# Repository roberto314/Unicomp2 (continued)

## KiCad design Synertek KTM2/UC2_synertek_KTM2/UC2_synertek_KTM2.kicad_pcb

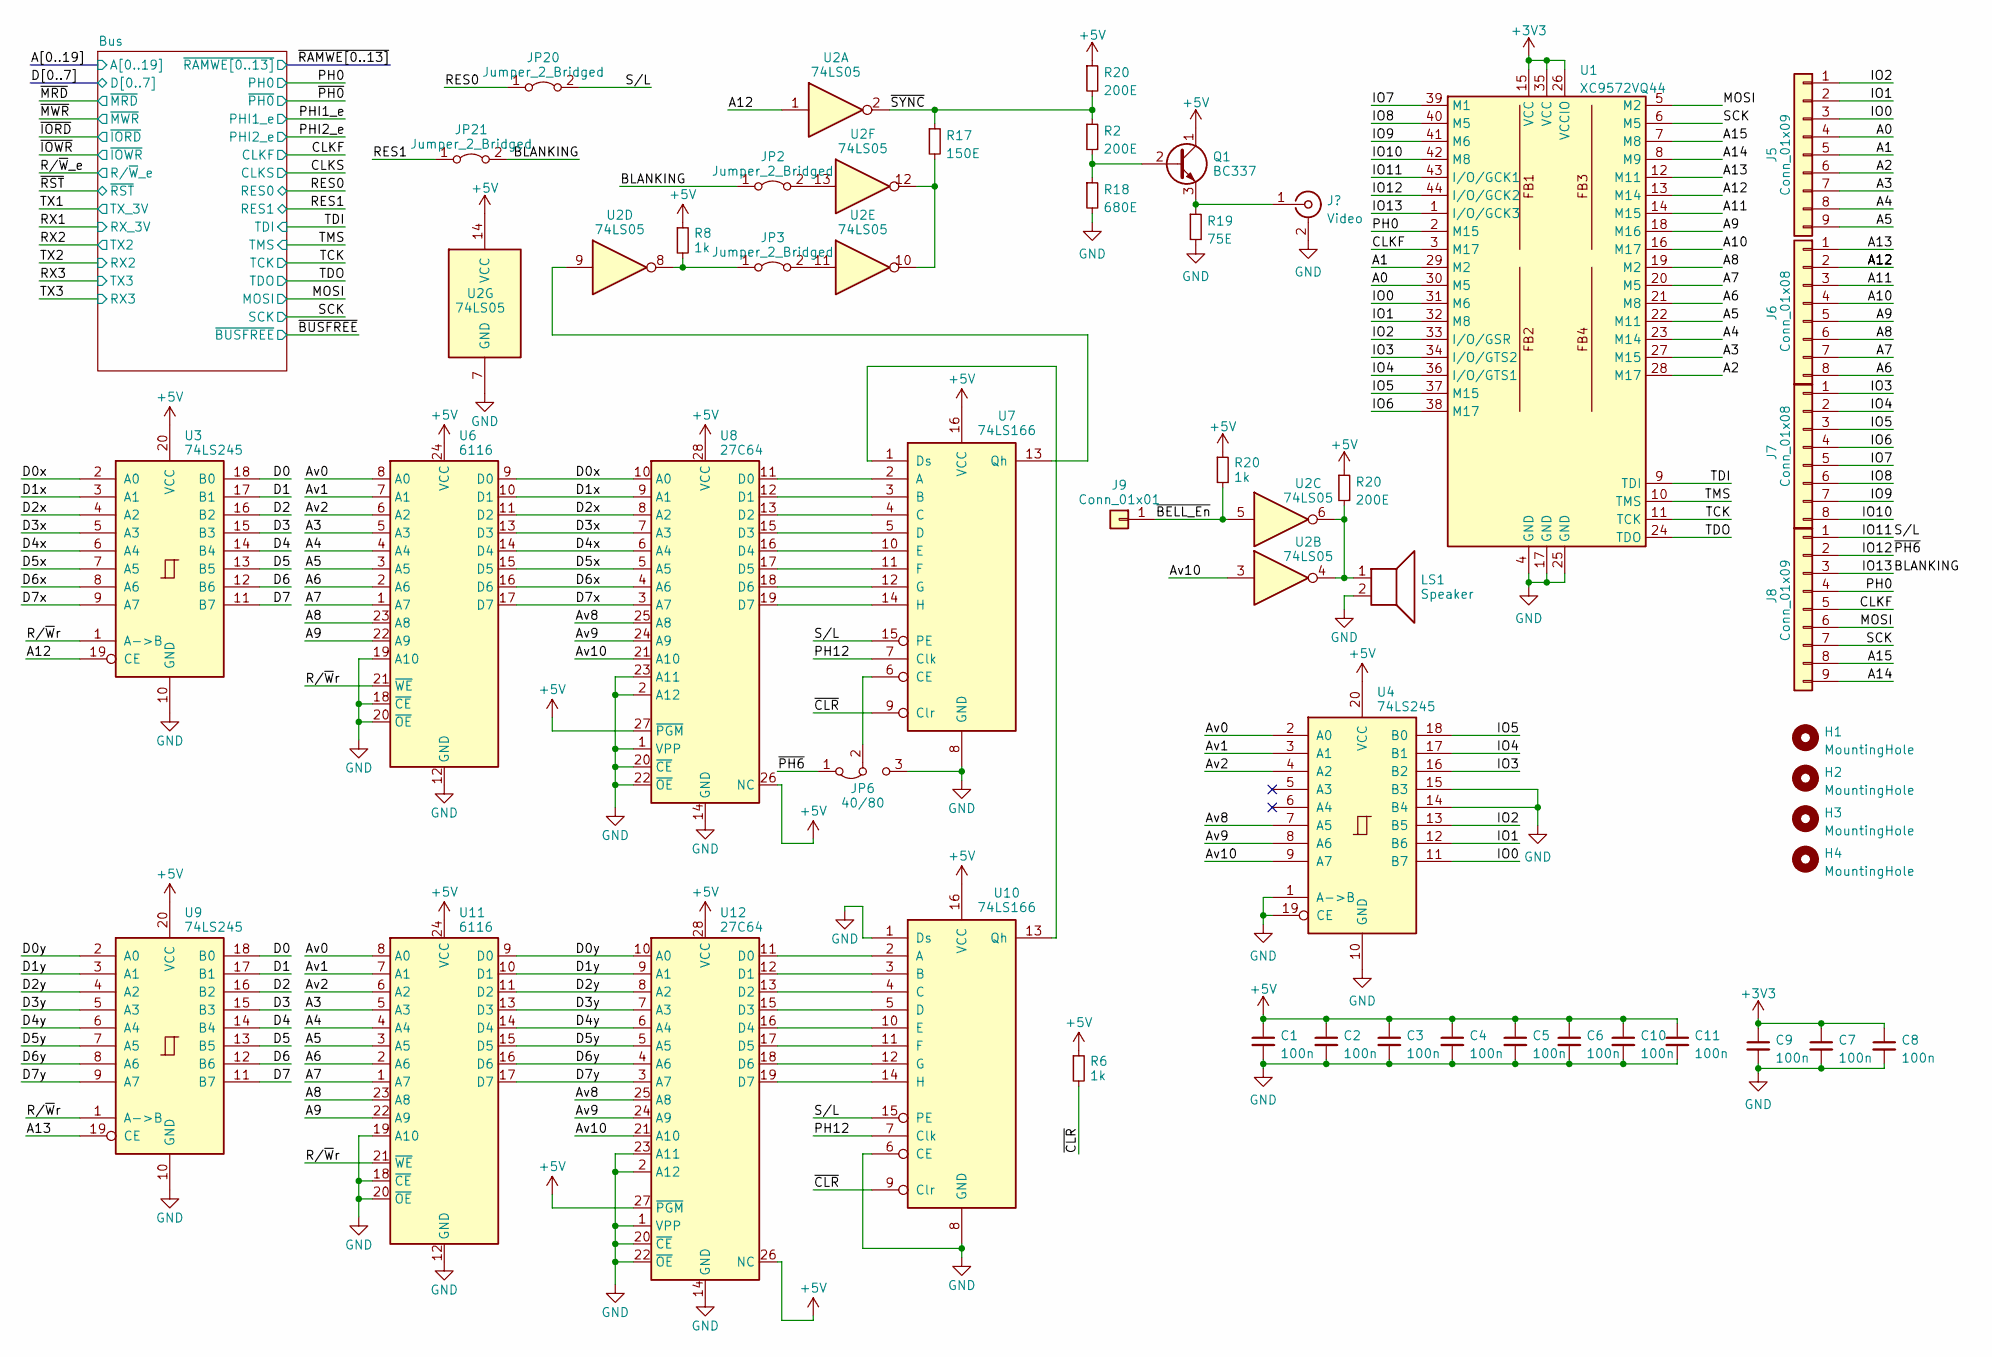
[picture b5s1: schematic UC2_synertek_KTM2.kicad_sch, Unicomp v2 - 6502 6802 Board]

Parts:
C1, C2, C3, C4, C5, C6, C7, C8, C9, C10, C11: 100n; C_1206_3216Metric
H1, H2, H3, H4: MountingHole; MountingHole_3.2mm_M3
J5, J8: Conn_01x09; PinHeader_1x09_P2.54mm_Vertical
J6, J7: Conn_01x08; PinHeader_1x08_P2.54mm_Vertical
J9: Conn_01x01; PinHeader_1x01_P2.54mm_Vertical
J20: Video; RCA-Jack
JP2, JP3, JP20, JP21: Jumper_2_Bridged; SolderJumper-2_P1.3mm_Bridged_RoundedPad1.0x1.5mm
JP6: 40/80; SolderJumper-3_P1.3mm_Bridged12_Pad1.0x1.5mm_NumberLabels
LS1: Speaker; MagneticBuzzer_Kingstate_KCG0601
Q1: BC337; TO-92_Inline
R2, R20: 200E; R_1206_3216Metric_Pad1.30x1.75mm_HandSolder
R6, R8: 1k; R_1206_3216Metric_Pad1.30x1.75mm_HandSolder
R17: 150E; R_1206_3216Metric_Pad1.30x1.75mm_HandSolder
R18: 680E; R_1206_3216Metric_Pad1.30x1.75mm_HandSolder
R19: 75E; R_1206_3216Metric_Pad1.30x1.75mm_HandSolder
U1: XC9572VQ44; TQFP-44_10x10mm_P0.8mm
U2: 74LS05; DIP-14_W7.62mm_LongPads
U3, U9: 74LS245; DIP-20_W7.62mm_LongPads
U4: 74LS245; SO-20_5.3x12.6mm_P1.27mm
U6, U11: 6116; DIP-24_W15.24mm_LongPads
U7, U10: 74LS166; DIP-16_W7.62mm_LongPads
U8, U12: 27C64; DIP-28_W15.24mm_LongPads

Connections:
+3V3: C7.1, C8.1, C9.1, U1.15 (VCC), U1.26 (VCCIO), U1.35 (VCC); also elsewhere on the board
+5V: C1.1, C2.1, C3.1, C4.1, C5.1, C6.1, C10.1, C11.1, Q1.1 (C), R6.1, R8.1, R20.1, U2.14 (VCC), U3.20 (VCC), U4.20 (VCC), U6.24 (VCC), U7.16 (VCC), U8.26 (NC), U8.27 (~PGM), U8.28 (VCC), U9.20 (VCC), U10.16 (VCC), U11.24 (VCC), U12.26 (NC), U12.27 (~PGM), U12.28 (VCC); also elsewhere on the board
/A0: J5.4, U1.30 (M5); also elsewhere on the board
/A1: J5.5, U1.29 (M2); also elsewhere on the board
/A2: J5.6, U1.28 (M17); also elsewhere on the board
/A3: J5.7, U1.27 (M15), U6.5 (A3), U11.5 (A3); also elsewhere on the board
/A4: J5.8, U1.23 (M14), U6.4 (A4), U11.4 (A4); also elsewhere on the board
/A5: J5.9, U1.22 (M11), U6.3 (A5), U11.3 (A5); also elsewhere on the board
/A6: J6.8, U1.21 (M8), U6.2 (A6), U11.2 (A6); also elsewhere on the board
/A7: J6.7, U1.20 (M5), U6.1 (A7), U11.1 (A7); also elsewhere on the board
/A8: J6.6, U1.19 (M2), U6.23 (A8), U11.23 (A8); also elsewhere on the board
/A9: J6.5, U1.18 (M16), U6.22 (A9), U11.22 (A9); also elsewhere on the board
/A10: J6.4, U1.16 (M17); also elsewhere on the board
/A11: J6.3, U1.14 (M15); also elsewhere on the board
/A12: J6.2, U1.13 (M14), U2.1, U3.19 (CE); also elsewhere on the board
/A13: J6.1, U1.12 (M11), U9.19 (CE); also elsewhere on the board
/A14: J8.9, U1.8 (M9); also elsewhere on the board
/A15: J8.8, U1.7 (M8); also elsewhere on the board
/Av0: U4.2 (A0), U6.8 (A0), U11.8 (A0)
/Av1: U4.3 (A1), U6.7 (A1), U11.7 (A1)
/Av2: U4.4 (A2), U6.6 (A2), U11.6 (A2)
/Av8: U4.7 (A5), U8.25 (A8), U12.25 (A8)
/Av9: U4.8 (A6), U8.24 (A9), U12.24 (A9)
/Av10: U2.3, U4.9 (A7), U8.21 (A10), U12.21 (A10)
/BLANKING: J8.3, JP2.1 (A), JP21.2 (B), U1.1 (I/O/GCK3)
/CLKF: J8.5, U1.3 (M17); also elsewhere on the board
/D0: U3.18 (B0), U9.18 (B0); also elsewhere on the board
/D0x: U3.2 (A0), U6.9 (D0), U8.10 (A0)
/D0y: U9.2 (A0), U11.9 (D0), U12.10 (A0)
/D1: U3.17 (B1), U9.17 (B1); also elsewhere on the board
/D1x: U3.3 (A1), U6.10 (D1), U8.9 (A1)
/D1y: U9.3 (A1), U11.10 (D1), U12.9 (A1)
/D2: U3.16 (B2), U9.16 (B2); also elsewhere on the board
/D2x: U3.4 (A2), U6.11 (D2), U8.8 (A2)
/D2y: U9.4 (A2), U11.11 (D2), U12.8 (A2)
/D3: U3.15 (B3), U9.15 (B3); also elsewhere on the board
/D3x: U3.5 (A3), U6.13 (D3), U8.7 (A3)
/D3y: U9.5 (A3), U11.13 (D3), U12.7 (A3)
/D4: U3.14 (B4), U9.14 (B4); also elsewhere on the board
/D4x: U3.6 (A4), U6.14 (D4), U8.6 (A4)
/D4y: U9.6 (A4), U11.14 (D4), U12.6 (A4)
/D5: U3.13 (B5), U9.13 (B5); also elsewhere on the board
/D5x: U3.7 (A5), U6.15 (D5), U8.5 (A5)
/D5y: U9.7 (A5), U11.15 (D5), U12.5 (A5)
/D6: U3.12 (B6), U9.12 (B6); also elsewhere on the board
/D6x: U3.8 (A6), U6.16 (D6), U8.4 (A6)
/D6y: U9.8 (A6), U11.16 (D6), U12.4 (A6)
/D7: U3.11 (B7), U9.11 (B7); also elsewhere on the board
/D7x: U3.9 (A7), U6.17 (D7), U8.3 (A7)
/D7y: U9.9 (A7), U11.17 (D7), U12.3 (A7)
/IO0: J5.3, U1.31 (M6), U4.11 (B7)
/IO1: J5.2, U1.32 (M8), U4.12 (B6)
/IO2: J5.1, U1.33 (I/O/GSR), U4.13 (B5)
/IO3: J7.1, U1.34 (I/O/GTS2), U4.16 (B2)
/IO4: J7.2, U1.36 (I/O/GTS1), U4.17 (B1)
/IO5: J7.3, U1.37 (M15), U4.18 (B0)
/IO6: J7.4, U1.38 (M17)
/IO7: J7.5, U1.39 (M1)
/IO8: J7.6, U1.40 (M5)
/IO9: J7.7, U1.41 (M6)
/IO10: J7.8, U1.42 (M8)
/IO11: J8.1, JP20.2 (B), U1.43 (I/O/GCK1), U7.15 (PE), U10.15 (PE)
/IO12: J8.2, JP6.1 (A), U1.44 (I/O/GCK2)
/MOSI: J8.6, U1.5 (M2); also elsewhere on the board
/PH0: J8.4, U1.2 (M15); also elsewhere on the board
/PH12: U7.7 (Clk), U10.7 (Clk)
/RES0: JP20.1 (A); also elsewhere on the board
/RES1: JP21.1 (A); also elsewhere on the board
/R/~Wr: U3.1 (A->B), U6.21 (~WE), U9.1 (A->B), U11.21 (~WE)
/SCK: J8.7, U1.6 (M5); also elsewhere on the board
/TCK: U1.11 (TCK); also elsewhere on the board
/TDI: U1.9 (TDI); also elsewhere on the board
/TDO: U1.24 (TDO); also elsewhere on the board
/TMS: U1.10 (TMS); also elsewhere on the board
/~CLR: R6.2, U7.9 (Clr), U10.9 (Clr)
GND: C1.2, C2.2, C3.2, C4.2, C5.2, C6.2, C7.2, C8.2, C9.2, C10.2, C11.2, J20.2 (Ext), JP6.3 (B), LS1.2, R18.2, R19.2, U1.4 (GND), U1.17 (GND), U1.25 (GND), U2.7 (GND), U3.10 (GND), U4.1 (A->B), U4.10 (GND), U4.14 (B4), U4.15 (B3), U4.19 (CE), U6.12 (GND), U6.18 (~CE), U6.19 (A10), U6.20 (~OE), U7.8 (GND), U8.1 (VPP), U8.2 (A12), U8.14 (GND), U8.20 (~CE), U8.22 (~OE), U8.23 (A11), U9.10 (GND), U10.1 (Ds), U10.6 (CE), U10.8 (GND), U11.12 (GND), U11.18 (~CE), U11.19 (A10), U11.20 (~OE), U12.1 (VPP), U12.2 (A12), U12.14 (GND), U12.20 (~CE), U12.22 (~OE), U12.23 (A11); also elsewhere on the board
unnamed: J20.1 (In), Q1.3 (E), R19.1
unnamed: JP2.2 (B), U2.13
unnamed: JP3.1 (A), R8.2, U2.8
unnamed: JP3.2 (B), U2.11
unnamed: JP6.2 (C), U7.6 (CE)
unnamed: Q1.2 (B), R2.2, R18.1
unnamed: R17.2, U2.10, U2.12
unnamed: U7.2 (A), U8.11 (D0)
unnamed: U7.3 (B), U8.12 (D1)
unnamed: U7.4 (C), U8.13 (D2)
unnamed: U7.5 (D), U8.15 (D3)
unnamed: U7.10 (E), U8.16 (D4)
unnamed: U7.11 (F), U8.17 (D5)
unnamed: U7.12 (G), U8.18 (D6)
unnamed: U7.14 (H), U8.19 (D7)
unnamed: U2.9, U7.13 (Qh)
unnamed: U10.2 (A), U12.11 (D0)
unnamed: U10.3 (B), U12.12 (D1)
unnamed: U10.4 (C), U12.13 (D2)
unnamed: U10.5 (D), U12.15 (D3)
unnamed: U10.10 (E), U12.16 (D4)
unnamed: U10.11 (F), U12.17 (D5)
unnamed: U10.12 (G), U12.18 (D6)
unnamed: U10.14 (H), U12.19 (D7)
unnamed: U7.1 (Ds), U10.13 (Qh)

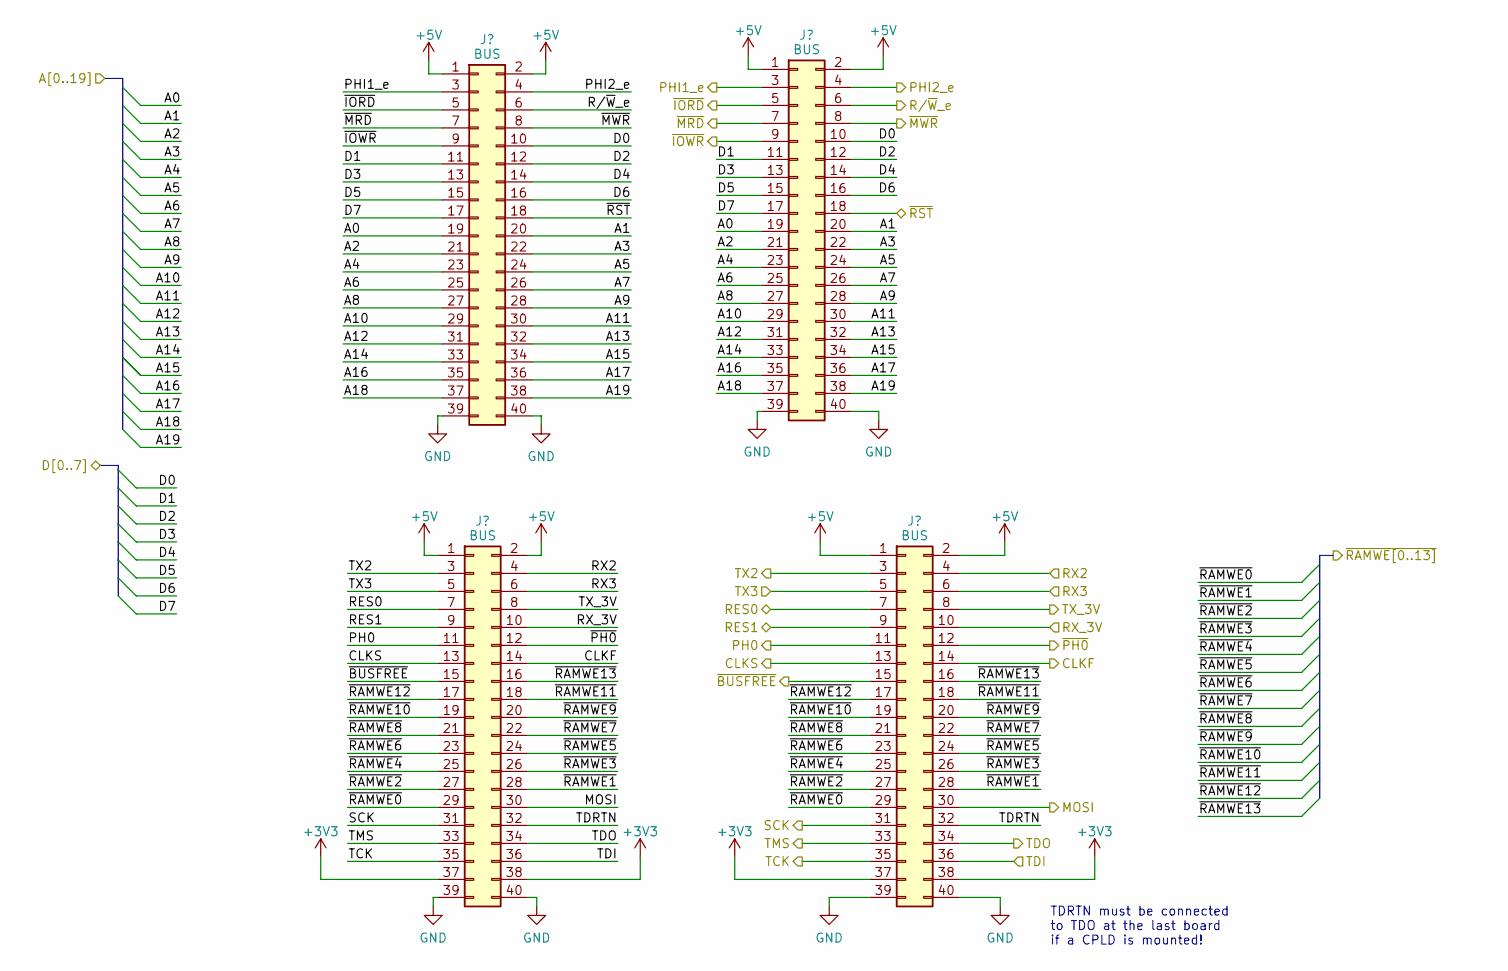
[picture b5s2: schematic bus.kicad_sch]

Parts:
J1, J2, J3, J4: BUS; PinSocket_2x20_P2.54mm_Vertical

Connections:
+3V3: J2.37, J2.38, J4.37, J4.38; also elsewhere on the board
+5V: J1.1, J1.2, J2.1, J2.2, J3.1, J3.2, J4.1, J4.2; also elsewhere on the board
/A0: J1.19, J3.19; also elsewhere on the board
/A1: J1.20, J3.20; also elsewhere on the board
/A2: J1.21, J3.21; also elsewhere on the board
/A3: J1.22, J3.22; also elsewhere on the board
/A4: J1.23, J3.23; also elsewhere on the board
/A5: J1.24, J3.24; also elsewhere on the board
/A6: J1.25, J3.25; also elsewhere on the board
/A7: J1.26, J3.26; also elsewhere on the board
/A8: J1.27, J3.27; also elsewhere on the board
/A9: J1.28, J3.28; also elsewhere on the board
/A10: J1.29, J3.29; also elsewhere on the board
/A11: J1.30, J3.30; also elsewhere on the board
/A12: J1.31, J3.31; also elsewhere on the board
/A13: J1.32, J3.32; also elsewhere on the board
/A14: J1.33, J3.33; also elsewhere on the board
/A15: J1.34, J3.34; also elsewhere on the board
/A16: J1.35, J3.35
/A17: J1.36, J3.36
/A18: J1.37, J3.37
/A19: J1.38, J3.38
/Bus/TDRTN: J2.32, J4.32
/CLKF: J2.14, J4.14; also elsewhere on the board
/CLKS: J2.13, J4.13
/D0: J1.10, J3.10; also elsewhere on the board
/D1: J1.11, J3.11; also elsewhere on the board
/D2: J1.12, J3.12; also elsewhere on the board
/D3: J1.13, J3.13; also elsewhere on the board
/D4: J1.14, J3.14; also elsewhere on the board
/D5: J1.15, J3.15; also elsewhere on the board
/D6: J1.16, J3.16; also elsewhere on the board
/D7: J1.17, J3.17; also elsewhere on the board
/MOSI: J2.30, J4.30; also elsewhere on the board
/PH0: J2.11, J4.11; also elsewhere on the board
/PHI1_e: J1.3, J3.3
/PHI2_e: J1.4, J3.4
/RES0: J2.7, J4.7; also elsewhere on the board
/RES1: J2.9, J4.9; also elsewhere on the board
/RX1: J2.10, J4.10
/RX2: J2.3, J4.3
/RX3: J2.5, J4.5
/R/~W_e: J1.6, J3.6
/SCK: J2.31, J4.31; also elsewhere on the board
/TCK: J2.35, J4.35; also elsewhere on the board
/TDI: J2.36, J4.36; also elsewhere on the board
/TDO: J2.34, J4.34; also elsewhere on the board
/TMS: J2.33, J4.33; also elsewhere on the board
/TX1: J2.8, J4.8
/TX2: J2.4, J4.4
/TX3: J2.6, J4.6
/~BUSFREE: J2.15, J4.15
/~IORD: J1.5, J3.5
/~IOWR: J1.9, J3.9
/~MRD: J1.7, J3.7
/~MWR: J1.8, J3.8
/~PH0: J2.12, J4.12
/~RAMWE0: J2.29, J4.29
/~RAMWE1: J2.28, J4.28
/~RAMWE2: J2.27, J4.27
/~RAMWE3: J2.26, J4.26
/~RAMWE4: J2.25, J4.25
/~RAMWE5: J2.24, J4.24
/~RAMWE6: J2.23, J4.23
/~RAMWE7: J2.22, J4.22
/~RAMWE8: J2.21, J4.21
/~RAMWE9: J2.20, J4.20
/~RAMWE10: J2.19, J4.19
/~RAMWE11: J2.18, J4.18
/~RAMWE12: J2.17, J4.17
/~RAMWE13: J2.16, J4.16
/~RST: J1.18, J3.18
GND: J1.39, J1.40, J2.39, J2.40, J3.39, J3.40, J4.39, J4.40; also elsewhere on the board

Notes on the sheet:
TDRTN must be connected to TDO at the last board if a CPLD is mounted!

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
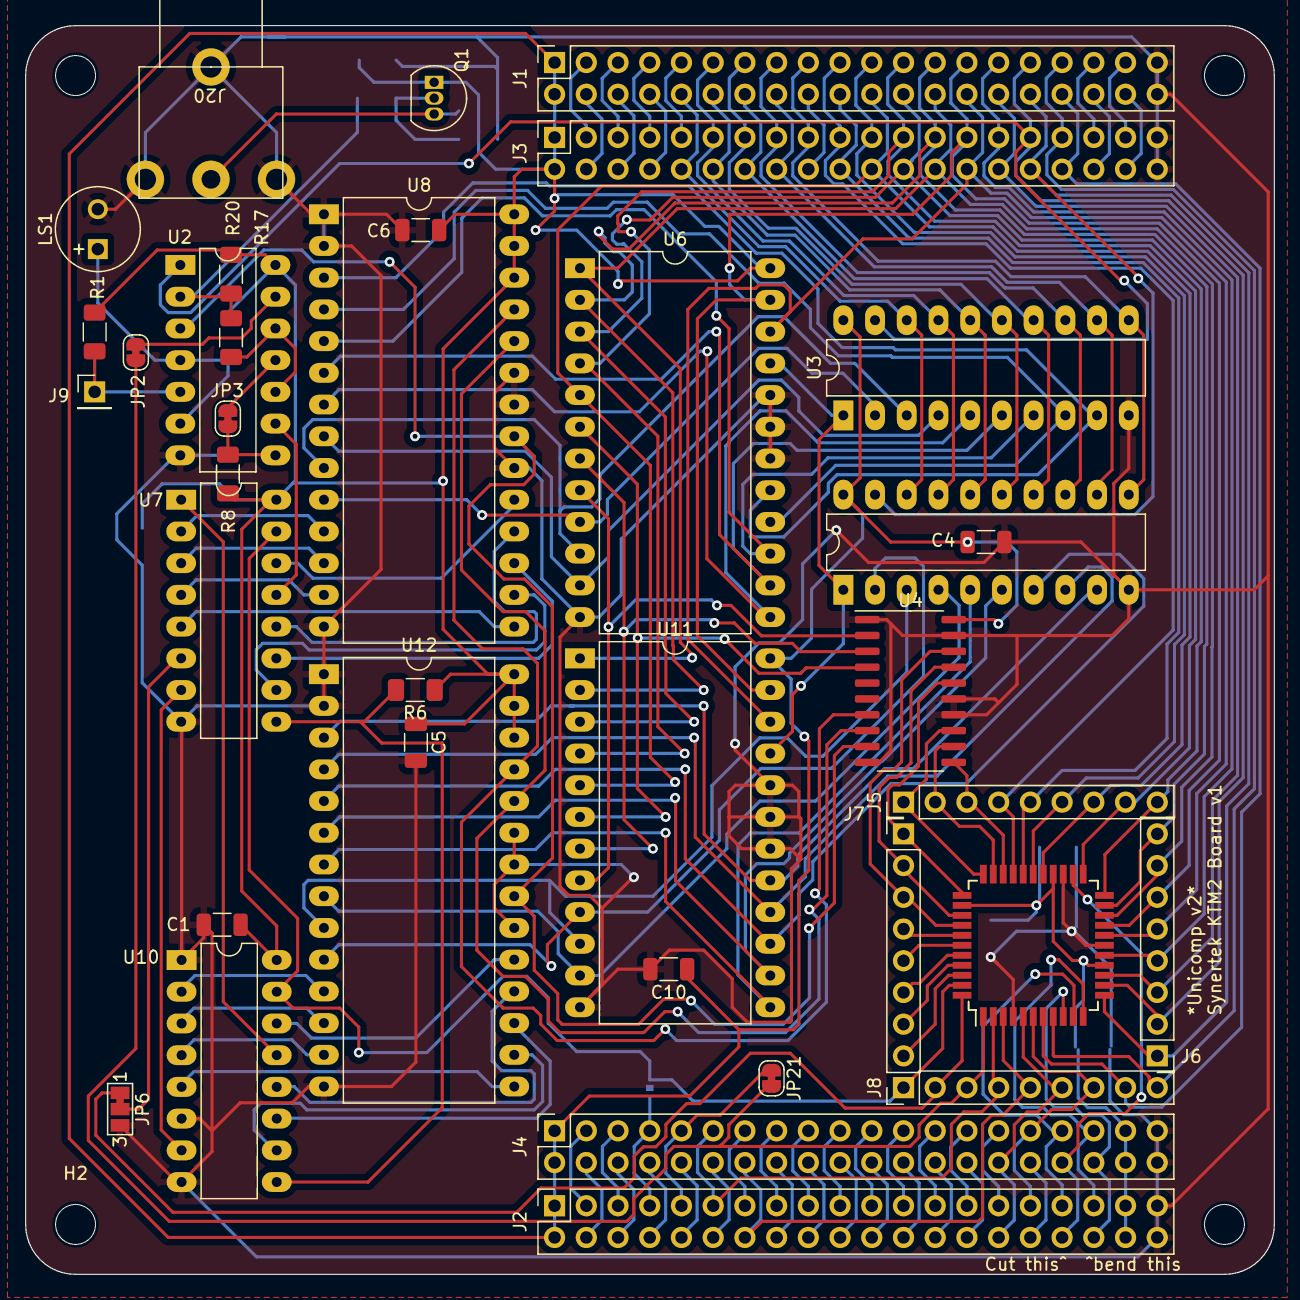
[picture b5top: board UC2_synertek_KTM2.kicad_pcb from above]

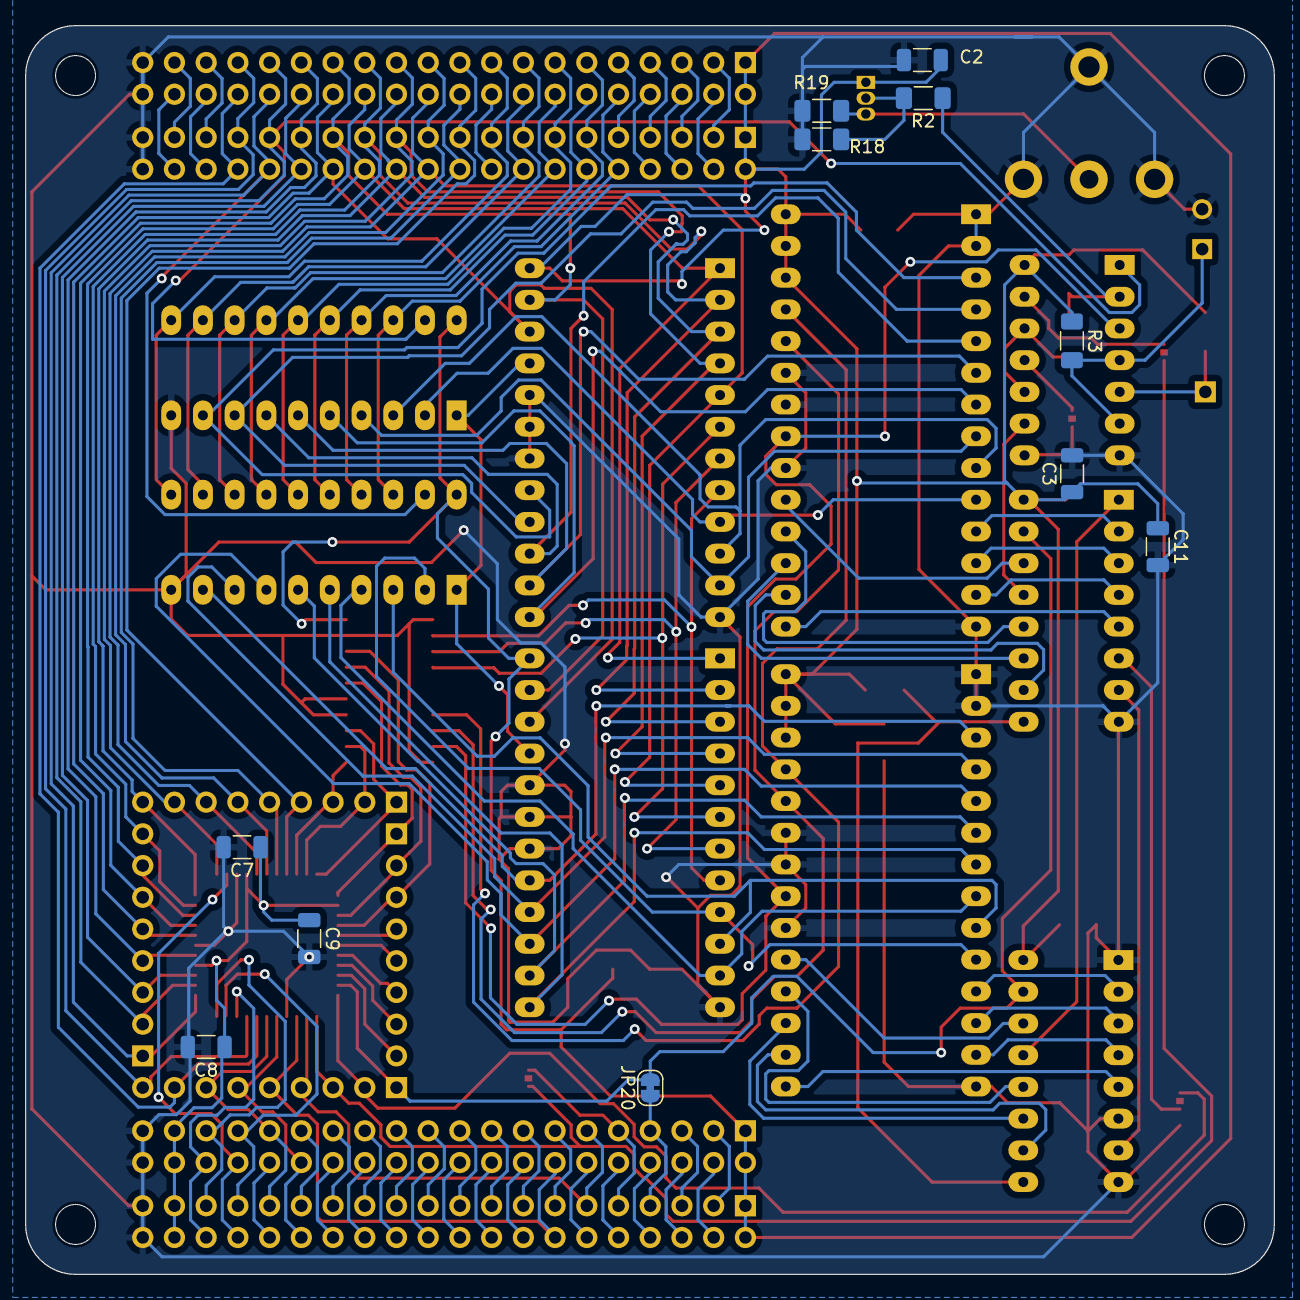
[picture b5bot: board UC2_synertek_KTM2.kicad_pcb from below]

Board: 2 copper layers, 100.0 x 100.0 mm, 52 parts (11 on the bottom side), 140 nets.

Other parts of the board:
R1: 1k; R_1206_3216Metric_Pad1.30x1.75mm_HandSolder
R3: 200E; R_1206_3216Metric_Pad1.30x1.75mm_HandSolder

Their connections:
+5V: R1.1, R3.1; also elsewhere on the board

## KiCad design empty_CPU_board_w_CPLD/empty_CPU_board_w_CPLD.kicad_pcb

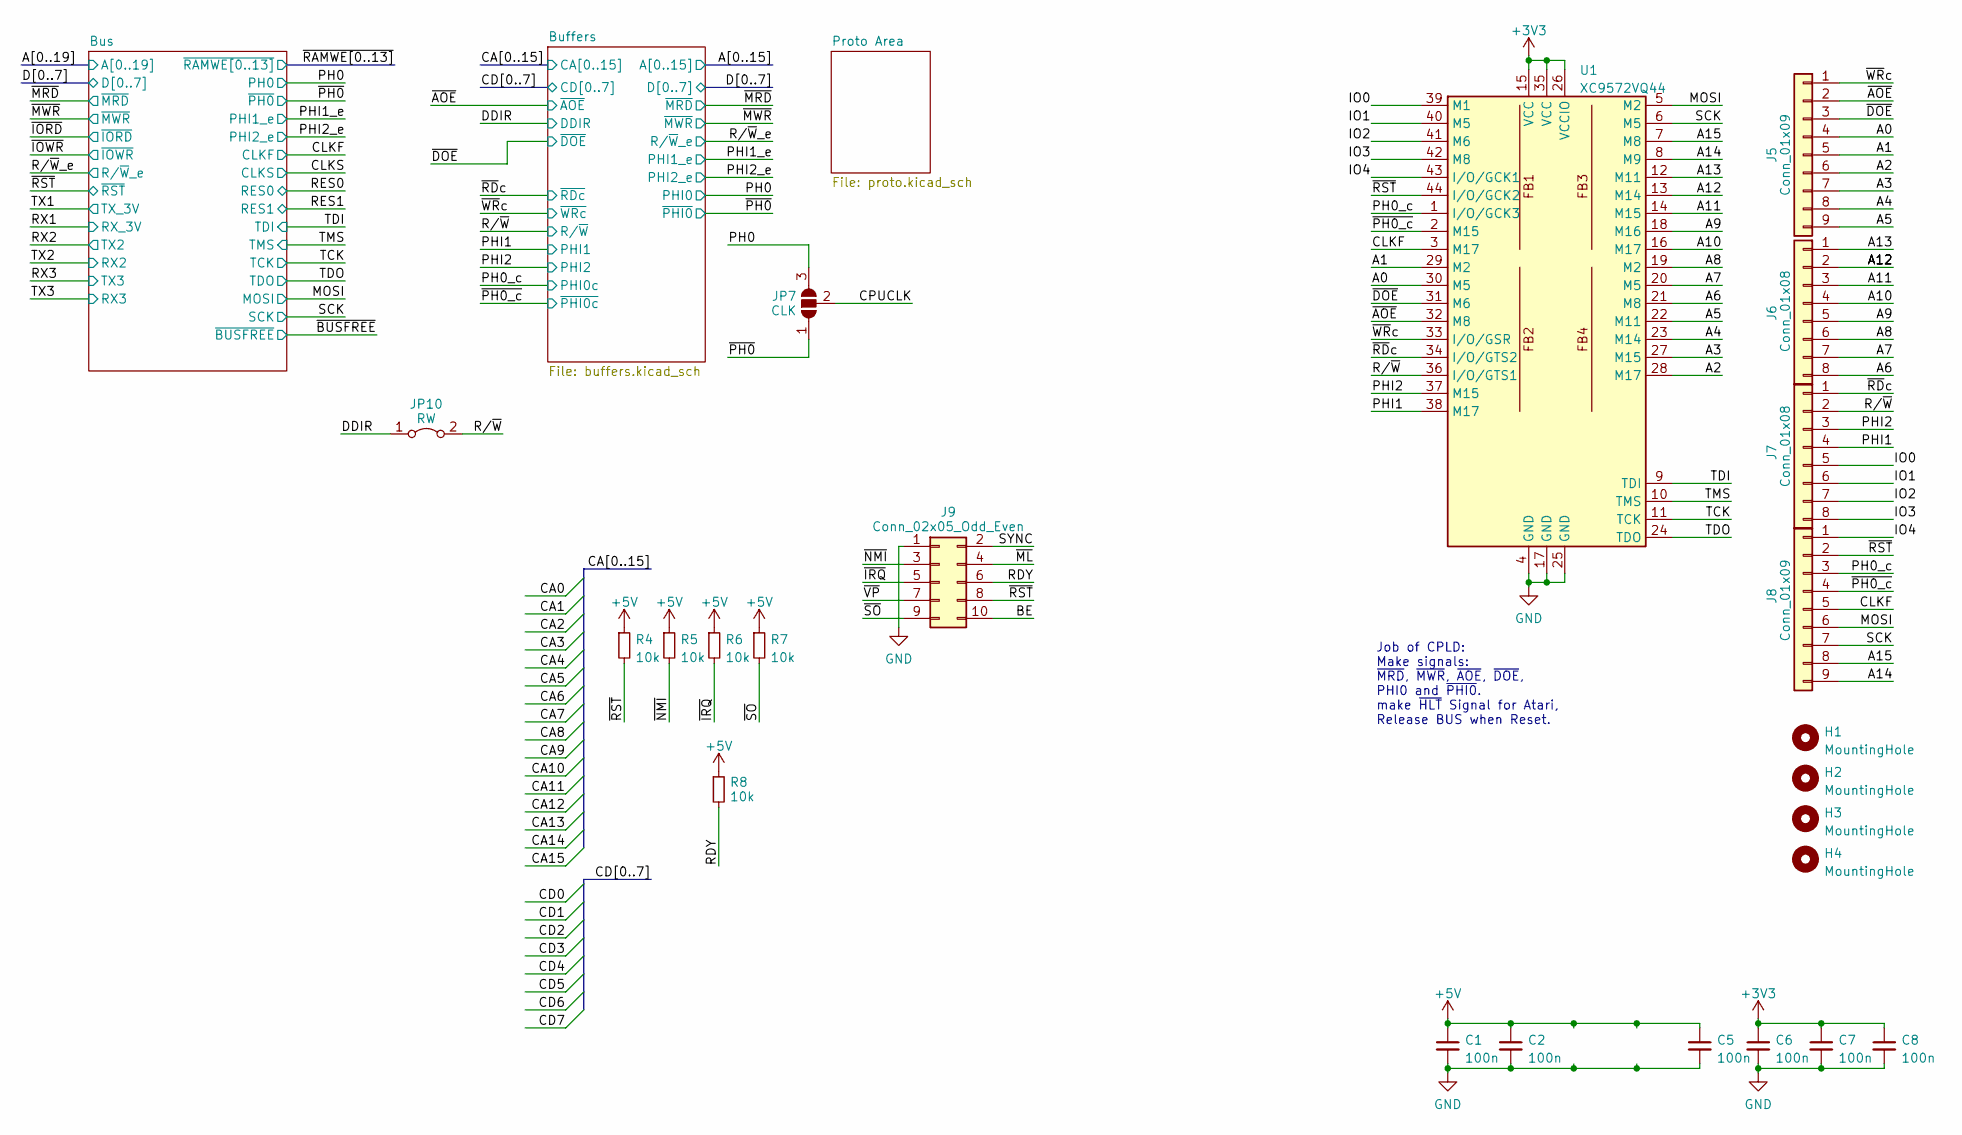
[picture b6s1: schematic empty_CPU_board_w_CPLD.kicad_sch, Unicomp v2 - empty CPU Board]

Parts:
C1, C2, C5, C6, C7, C8: 100n; C_1206_3216Metric
H1, H2, H3, H4: MountingHole; MountingHole_3.2mm_M3
J5, J8: Conn_01x09; PinHeader_1x09_P2.54mm_Vertical
J6, J7: Conn_01x08; PinHeader_1x08_P2.54mm_Vertical
J9: Conn_02x05_Odd_Even; PinHeader_2x05_P2.54mm_Horizontal
JP7: CLK; SolderJumper-3_P1.3mm_Open_RoundedPad1.0x1.5mm_NumberLabels
JP10: RW; SolderJumper-2_P1.3mm_Bridged_RoundedPad1.0x1.5mm
R4, R5, R6, R7, R8: 10k; R_1206_3216Metric_Pad1.30x1.75mm_HandSolder
U1: XC9572VQ44; TQFP-44_10x10mm_P0.8mm

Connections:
+3V3: C6.1, C7.1, C8.1, U1.15 (VCC), U1.26 (VCCIO), U1.35 (VCC); also elsewhere on the board
+5V: C1.1, C2.1, C5.1, R4.1, R5.1, R6.1, R7.1, R8.1; also elsewhere on the board
/A0: J5.4, U1.30 (M5); also elsewhere on the board
/A1: J5.5, U1.29 (M2); also elsewhere on the board
/A2: J5.6, U1.28 (M17); also elsewhere on the board
/A3: J5.7, U1.27 (M15); also elsewhere on the board
/A4: J5.8, U1.23 (M14); also elsewhere on the board
/A5: J5.9, U1.22 (M11); also elsewhere on the board
/A6: J6.8, U1.21 (M8); also elsewhere on the board
/A7: J6.7, U1.20 (M5); also elsewhere on the board
/A8: J6.6, U1.19 (M2); also elsewhere on the board
/A9: J6.5, U1.18 (M16); also elsewhere on the board
/A10: J6.4, U1.16 (M17); also elsewhere on the board
/A11: J6.3, U1.14 (M15); also elsewhere on the board
/A12: J6.2, U1.13 (M14); also elsewhere on the board
/A13: J6.1, U1.12 (M11); also elsewhere on the board
/A14: J8.9, U1.8 (M9); also elsewhere on the board
/A15: J8.8, U1.7 (M8); also elsewhere on the board
/BE: J9.10
/CLKF: J8.5, U1.3 (M17); also elsewhere on the board
/CPUCLK: JP7.2 (C)
/DDIR: JP10.1 (A); also elsewhere on the board
/IO0: J7.5, U1.39 (M1)
/IO1: J7.6, U1.40 (M5)
/IO2: J7.7, U1.41 (M6)
/IO3: J7.8, U1.42 (M8)
/IO4: J8.1, U1.43 (I/O/GCK1)
/MOSI: J8.6, U1.5 (M2); also elsewhere on the board
/PH0: JP7.3 (B); also elsewhere on the board
/PH0_c: J8.3, U1.1 (I/O/GCK3); also elsewhere on the board
/PHI1: J7.4, U1.38 (M17); also elsewhere on the board
/PHI2: J7.3, U1.37 (M15); also elsewhere on the board
/RDY: J9.6, R8.2
/R/~W: J7.2, JP10.2 (B), U1.36 (I/O/GTS1); also elsewhere on the board
/SCK: J8.7, U1.6 (M5); also elsewhere on the board
/SYNC: J9.2
/TCK: U1.11 (TCK); also elsewhere on the board
/TDI: U1.9 (TDI); also elsewhere on the board
/TDO: U1.24 (TDO); also elsewhere on the board
/TMS: U1.10 (TMS); also elsewhere on the board
/~AOE: J5.2, U1.32 (M8); also elsewhere on the board
/~DOE: J5.3, U1.31 (M6); also elsewhere on the board
/~IRQ: J9.5, R6.2
/~ML: J9.4
/~NMI: J9.3, R5.2
/~PH0_c: J8.4, U1.2 (M15); also elsewhere on the board
/~PH0: JP7.1 (A); also elsewhere on the board
/~RDc: J7.1, U1.34 (I/O/GTS2); also elsewhere on the board
/~RST: J8.2, J9.8, R4.2, U1.44 (I/O/GCK2); also elsewhere on the board
/~SO: J9.9, R7.2
/~VP: J9.7
/~WRc: J5.1, U1.33 (I/O/GSR); also elsewhere on the board
GND: C1.2, C2.2, C5.2, C6.2, C7.2, C8.2, J9.1, U1.4 (GND), U1.17 (GND), U1.25 (GND); also elsewhere on the board

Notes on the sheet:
Job of CPLD: Make signals: ~{MRD}, ~{MWR}, ~{AOE}, ~{DOE}, PHI0 and ~{PHI0}. make ~{HLT} Signal for Atari, Release BUS when Reset.

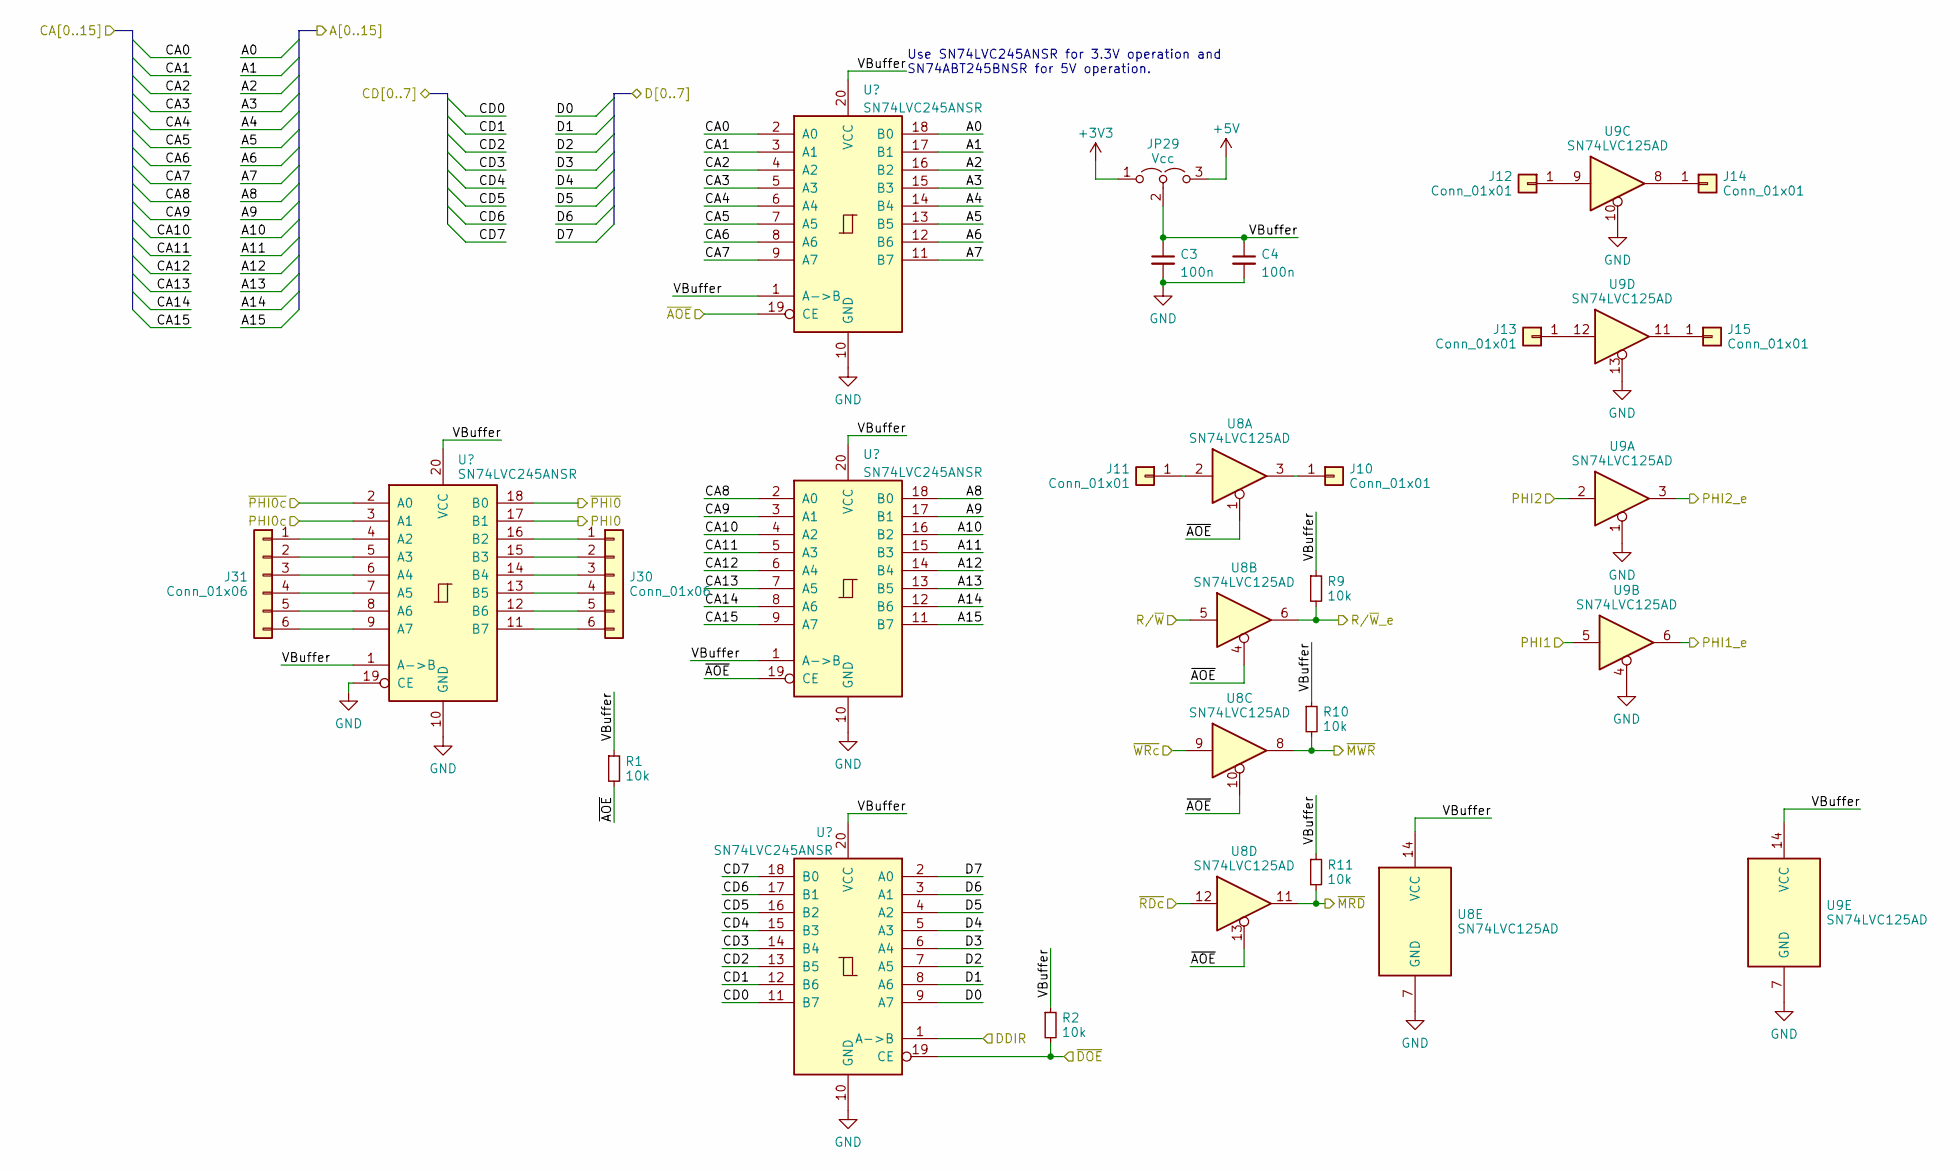
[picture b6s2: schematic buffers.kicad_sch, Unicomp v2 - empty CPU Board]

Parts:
C3, C4: 100n; C_1206_3216Metric
J10, J11, J12, J13, J14, J15: Conn_01x01; PinHeader_1x01_P1.27mm_Vertical
J30, J31: Conn_01x06; PinHeader_1x06_P1.27mm_Vertical
JP29: Vcc; SolderJumper-3_P1.3mm_Open_RoundedPad1.0x1.5mm_NumberLabels
R1, R2, R9, R10, R11: 10k; R_1206_3216Metric_Pad1.30x1.75mm_HandSolder
U2, U3, U4, U6: SN74LVC245ANSR; SO-20_5.3x12.6mm_P1.27mm
U8, U9: SN74LVC125AD; SOIC-14_3.9x8.7mm_P1.27mm

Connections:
+3V3: JP29.1 (A); also elsewhere on the board
+5V: JP29.3 (B); also elsewhere on the board
/A0: U2.18 (B0); also elsewhere on the board
/A1: U2.17 (B1); also elsewhere on the board
/A2: U2.16 (B2); also elsewhere on the board
/A3: U2.15 (B3); also elsewhere on the board
/A4: U2.14 (B4); also elsewhere on the board
/A5: U2.13 (B5); also elsewhere on the board
/A6: U2.12 (B6); also elsewhere on the board
/A7: U2.11 (B7); also elsewhere on the board
/A8: U3.18 (B0); also elsewhere on the board
/A9: U3.17 (B1); also elsewhere on the board
/A10: U3.16 (B2); also elsewhere on the board
/A11: U3.15 (B3); also elsewhere on the board
/A12: U3.14 (B4); also elsewhere on the board
/A13: U3.13 (B5); also elsewhere on the board
/A14: U3.12 (B6); also elsewhere on the board
/A15: U3.11 (B7); also elsewhere on the board
/Buffers/VBuffer: C3.1, C4.1, JP29.2 (C), R1.1, R2.1, R9.1, R10.1, R11.1, U2.1 (A->B), U2.20 (VCC), U3.1 (A->B), U3.20 (VCC), U4.20 (VCC), U6.1 (A->B), U6.20 (VCC), U8.14 (VCC), U9.14 (VCC)
/CA0: U2.2 (A0)
/CA1: U2.3 (A1)
/CA2: U2.4 (A2)
/CA3: U2.5 (A3)
/CA4: U2.6 (A4)
/CA5: U2.7 (A5)
/CA6: U2.8 (A6)
/CA7: U2.9 (A7)
/CA8: U3.2 (A0)
/CA9: U3.3 (A1)
/CA10: U3.4 (A2)
/CA11: U3.5 (A3)
/CA12: U3.6 (A4)
/CA13: U3.7 (A5)
/CA14: U3.8 (A6)
/CA15: U3.9 (A7)
/CD0: U4.11 (B7)
/CD1: U4.12 (B6)
/CD2: U4.13 (B5)
/CD3: U4.14 (B4)
/CD4: U4.15 (B3)
/CD5: U4.16 (B2)
/CD6: U4.17 (B1)
/CD7: U4.18 (B0)
/D0: U4.9 (A7); also elsewhere on the board
/D1: U4.8 (A6); also elsewhere on the board
/D2: U4.7 (A5); also elsewhere on the board
/D3: U4.6 (A4); also elsewhere on the board
/D4: U4.5 (A3); also elsewhere on the board
/D5: U4.4 (A2); also elsewhere on the board
/D6: U4.3 (A1); also elsewhere on the board
/D7: U4.2 (A0); also elsewhere on the board
/DDIR: U4.1 (A->B); also elsewhere on the board
/PH0: U6.17 (B1); also elsewhere on the board
/PH0_c: U6.3 (A1); also elsewhere on the board
/PHI1: U9.5; also elsewhere on the board
/PHI1_e: U9.6; also elsewhere on the board
/PHI2: U9.2; also elsewhere on the board
/PHI2_e: U9.3; also elsewhere on the board
/R/~W: U8.5; also elsewhere on the board
/R/~W_e: R9.2, U8.6; also elsewhere on the board
/~AOE: R1.2, U2.19 (CE), U3.19 (CE), U8.1, U8.4, U8.10, U8.13; also elsewhere on the board
/~DOE: R2.2, U4.19 (CE); also elsewhere on the board
/~MRD: R11.2, U8.11; also elsewhere on the board
/~MWR: R10.2, U8.8; also elsewhere on the board
/~PH0_c: U6.2 (A0); also elsewhere on the board
/~PH0: U6.18 (B0); also elsewhere on the board
/~RDc: U8.12; also elsewhere on the board
/~WRc: U8.9; also elsewhere on the board
GND: C3.2, C4.2, U2.10 (GND), U3.10 (GND), U4.10 (GND), U6.10 (GND), U6.19 (CE), U8.7 (GND), U9.1, U9.4, U9.7 (GND), U9.10, U9.13; also elsewhere on the board
unnamed: J10.1, U8.3
unnamed: J11.1, U8.2
unnamed: J12.1, U9.9
unnamed: J13.1, U9.12
unnamed: J14.1, U9.8
unnamed: J15.1, U9.11
unnamed: J30.1, U6.16 (B2)
unnamed: J30.2, U6.15 (B3)
unnamed: J30.3, U6.14 (B4)
unnamed: J30.4, U6.13 (B5)
unnamed: J30.5, U6.12 (B6)
unnamed: J30.6, U6.11 (B7)
unnamed: J31.1, U6.4 (A2)
unnamed: J31.2, U6.5 (A3)
unnamed: J31.3, U6.6 (A4)
unnamed: J31.4, U6.7 (A5)
unnamed: J31.5, U6.8 (A6)
unnamed: J31.6, U6.9 (A7)

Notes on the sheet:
Use SN74LVC245ANSR for 3.3V operation and SN74ABT245BNSR for 5V operation.
